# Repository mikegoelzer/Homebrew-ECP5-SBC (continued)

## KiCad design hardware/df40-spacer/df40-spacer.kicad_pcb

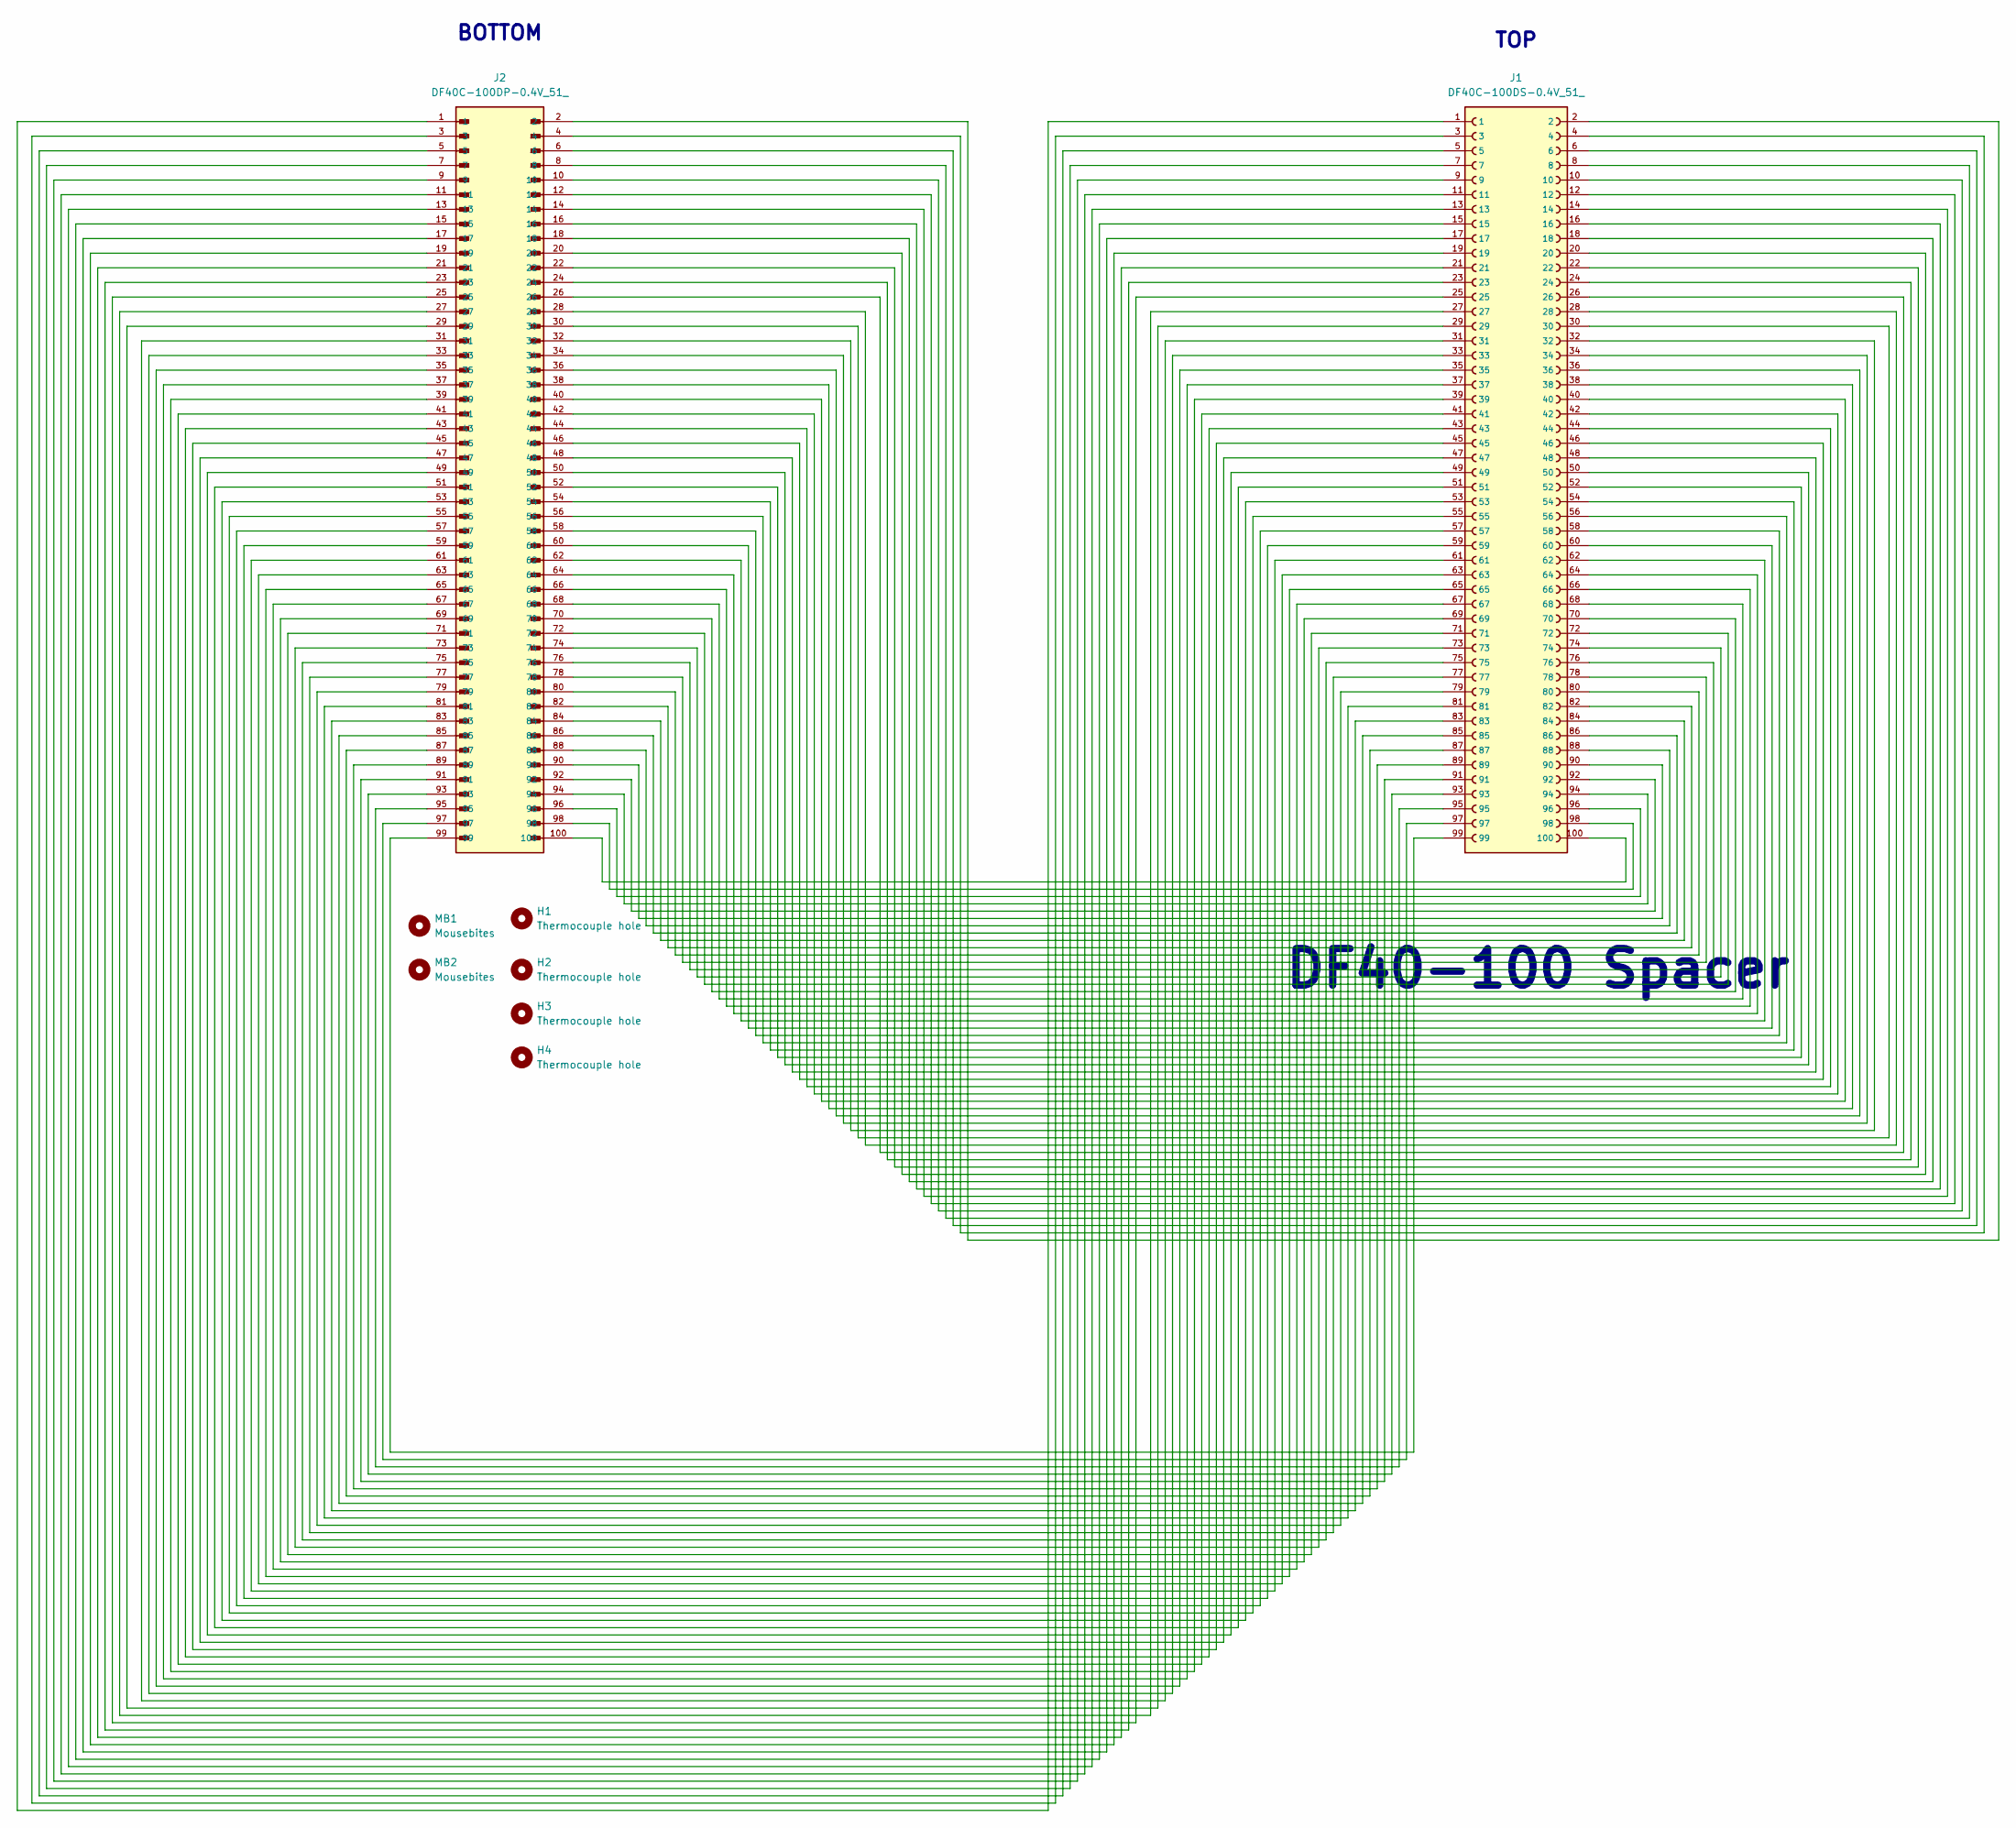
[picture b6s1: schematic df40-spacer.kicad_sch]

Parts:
H1, H2, H3, H4: Thermocouple hole; MountingHole_2.7mm_M2.5
J1: DF40C-100DS-0.4V_51_; HIROSE_DF40C-100DS-0.4V_51_; PARTREV Oct.1.2023
J2: DF40C-100DP-0.4V_51_; HIROSE_DF40C-100DP-0.4V_51_; MPN DF40C-100DP-0.4V(51)
MB1, MB2: Mousebites; mouse-bite-2.54mm-slot

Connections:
unnamed: J1.1, J2.1
unnamed: J1.2, J2.2
unnamed: J1.3, J2.3
unnamed: J1.4, J2.4
unnamed: J1.5, J2.5
unnamed: J1.6, J2.6
unnamed: J1.7, J2.7
unnamed: J1.8, J2.8
unnamed: J1.9, J2.9
unnamed: J1.10, J2.10
unnamed: J1.11, J2.11
unnamed: J1.12, J2.12
unnamed: J1.13, J2.13
unnamed: J1.14, J2.14
unnamed: J1.15, J2.15
unnamed: J1.16, J2.16
unnamed: J1.17, J2.17
unnamed: J1.18, J2.18
unnamed: J1.19, J2.19
unnamed: J1.20, J2.20
unnamed: J1.21, J2.21
unnamed: J1.22, J2.22
unnamed: J1.23, J2.23
unnamed: J1.24, J2.24
unnamed: J1.25, J2.25
unnamed: J1.26, J2.26
unnamed: J1.27, J2.27
unnamed: J1.28, J2.28
unnamed: J1.29, J2.29
unnamed: J1.30, J2.30
unnamed: J1.31, J2.31
unnamed: J1.32, J2.32
unnamed: J1.33, J2.33
unnamed: J1.34, J2.34
unnamed: J1.35, J2.35
unnamed: J1.36, J2.36
unnamed: J1.37, J2.37
unnamed: J1.38, J2.38
unnamed: J1.39, J2.39
unnamed: J1.40, J2.40
unnamed: J1.41, J2.41
unnamed: J1.42, J2.42
unnamed: J1.43, J2.43
unnamed: J1.44, J2.44
unnamed: J1.45, J2.45
unnamed: J1.46, J2.46
unnamed: J1.47, J2.47
unnamed: J1.48, J2.48
unnamed: J1.49, J2.49
unnamed: J1.50, J2.50
unnamed: J1.51, J2.51
unnamed: J1.52, J2.52
unnamed: J1.53, J2.53
unnamed: J1.54, J2.54
unnamed: J1.55, J2.55
unnamed: J1.56, J2.56
unnamed: J1.57, J2.57
unnamed: J1.58, J2.58
unnamed: J1.59, J2.59
unnamed: J1.60, J2.60
unnamed: J1.61, J2.61
unnamed: J1.62, J2.62
unnamed: J1.63, J2.63
unnamed: J1.64, J2.64
unnamed: J1.65, J2.65
unnamed: J1.66, J2.66
unnamed: J1.67, J2.67
unnamed: J1.68, J2.68
unnamed: J1.69, J2.69
unnamed: J1.70, J2.70
unnamed: J1.71, J2.71
unnamed: J1.72, J2.72
unnamed: J1.73, J2.73
unnamed: J1.74, J2.74
unnamed: J1.75, J2.75
unnamed: J1.76, J2.76
unnamed: J1.77, J2.77
unnamed: J1.78, J2.78
unnamed: J1.79, J2.79
unnamed: J1.80, J2.80
unnamed: J1.81, J2.81
unnamed: J1.82, J2.82
unnamed: J1.83, J2.83
unnamed: J1.84, J2.84
unnamed: J1.85, J2.85
unnamed: J1.86, J2.86
unnamed: J1.87, J2.87
unnamed: J1.88, J2.88
unnamed: J1.89, J2.89
unnamed: J1.90, J2.90
unnamed: J1.91, J2.91
unnamed: J1.92, J2.92
unnamed: J1.93, J2.93
unnamed: J1.94, J2.94
unnamed: J1.95, J2.95
unnamed: J1.96, J2.96
unnamed: J1.97, J2.97
unnamed: J1.98, J2.98
unnamed: J1.99, J2.99
unnamed: J1.100, J2.100

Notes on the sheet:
DF40-100 Spacer
TOP
BOTTOM

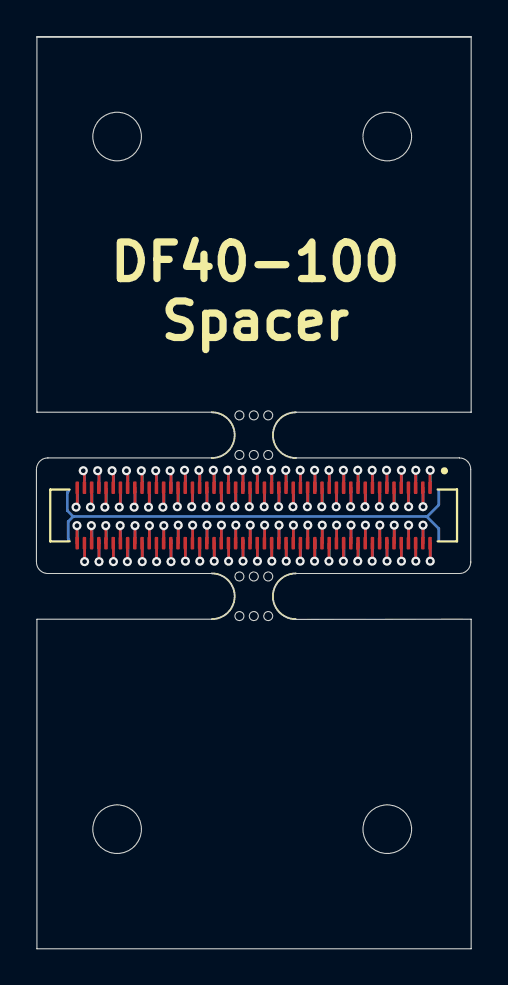
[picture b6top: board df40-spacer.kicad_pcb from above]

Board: 2 copper layers, 24.2 x 50.7 mm, 8 parts (1 on the bottom side), 100 nets.

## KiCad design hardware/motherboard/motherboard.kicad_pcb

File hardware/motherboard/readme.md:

# Motherboard

This is the motherboard of the computer.  The Compute Module snaps into it to provide the computer's CPU and memory.  The motherboard then provides:

- HDMI
- VGA
- JTAG
- USB debug interface
- PMOD connectors
- Expansion slots for custom PCBs
- FFC connector to connect to the hat board that provides the touch screen
- SD card slot for the computer's "hard drive"
- Boot flash for the FPGA
- 5V power input
- Diagnostic LEDs and switches
- 100-pin Hirose female connectors for the Compute Module to snap into

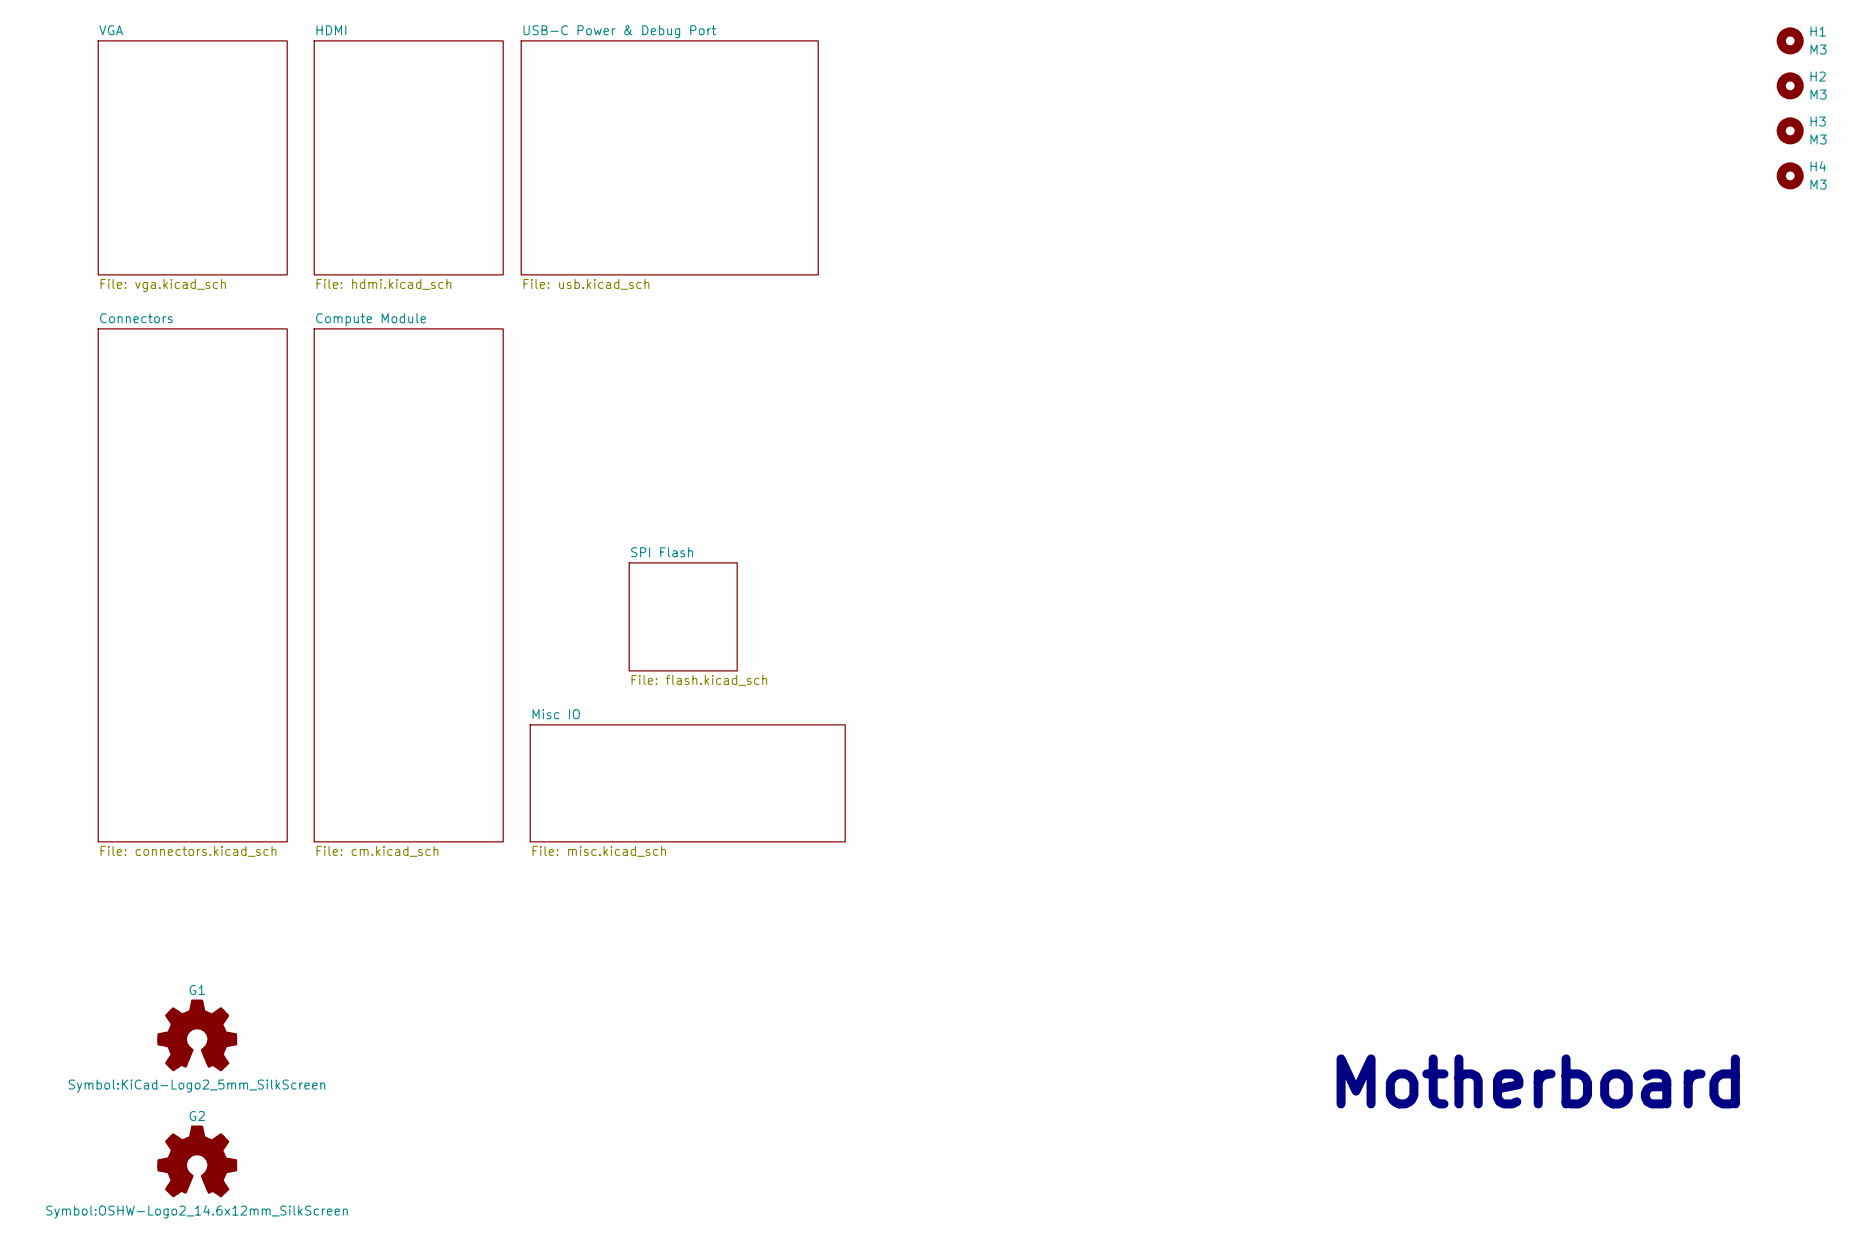
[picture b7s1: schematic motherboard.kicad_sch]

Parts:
G1: Logo_Open_Hardware_Small; KiCad-Logo2_5mm_SilkScreen
G2: Logo_Open_Hardware_Small; OSHW-Logo2_14.6x12mm_SilkScreen
H1, H2, H3, H4: M3; MountingHole_3.2mm_M3; MPN 97790603111

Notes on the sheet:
Motherboard

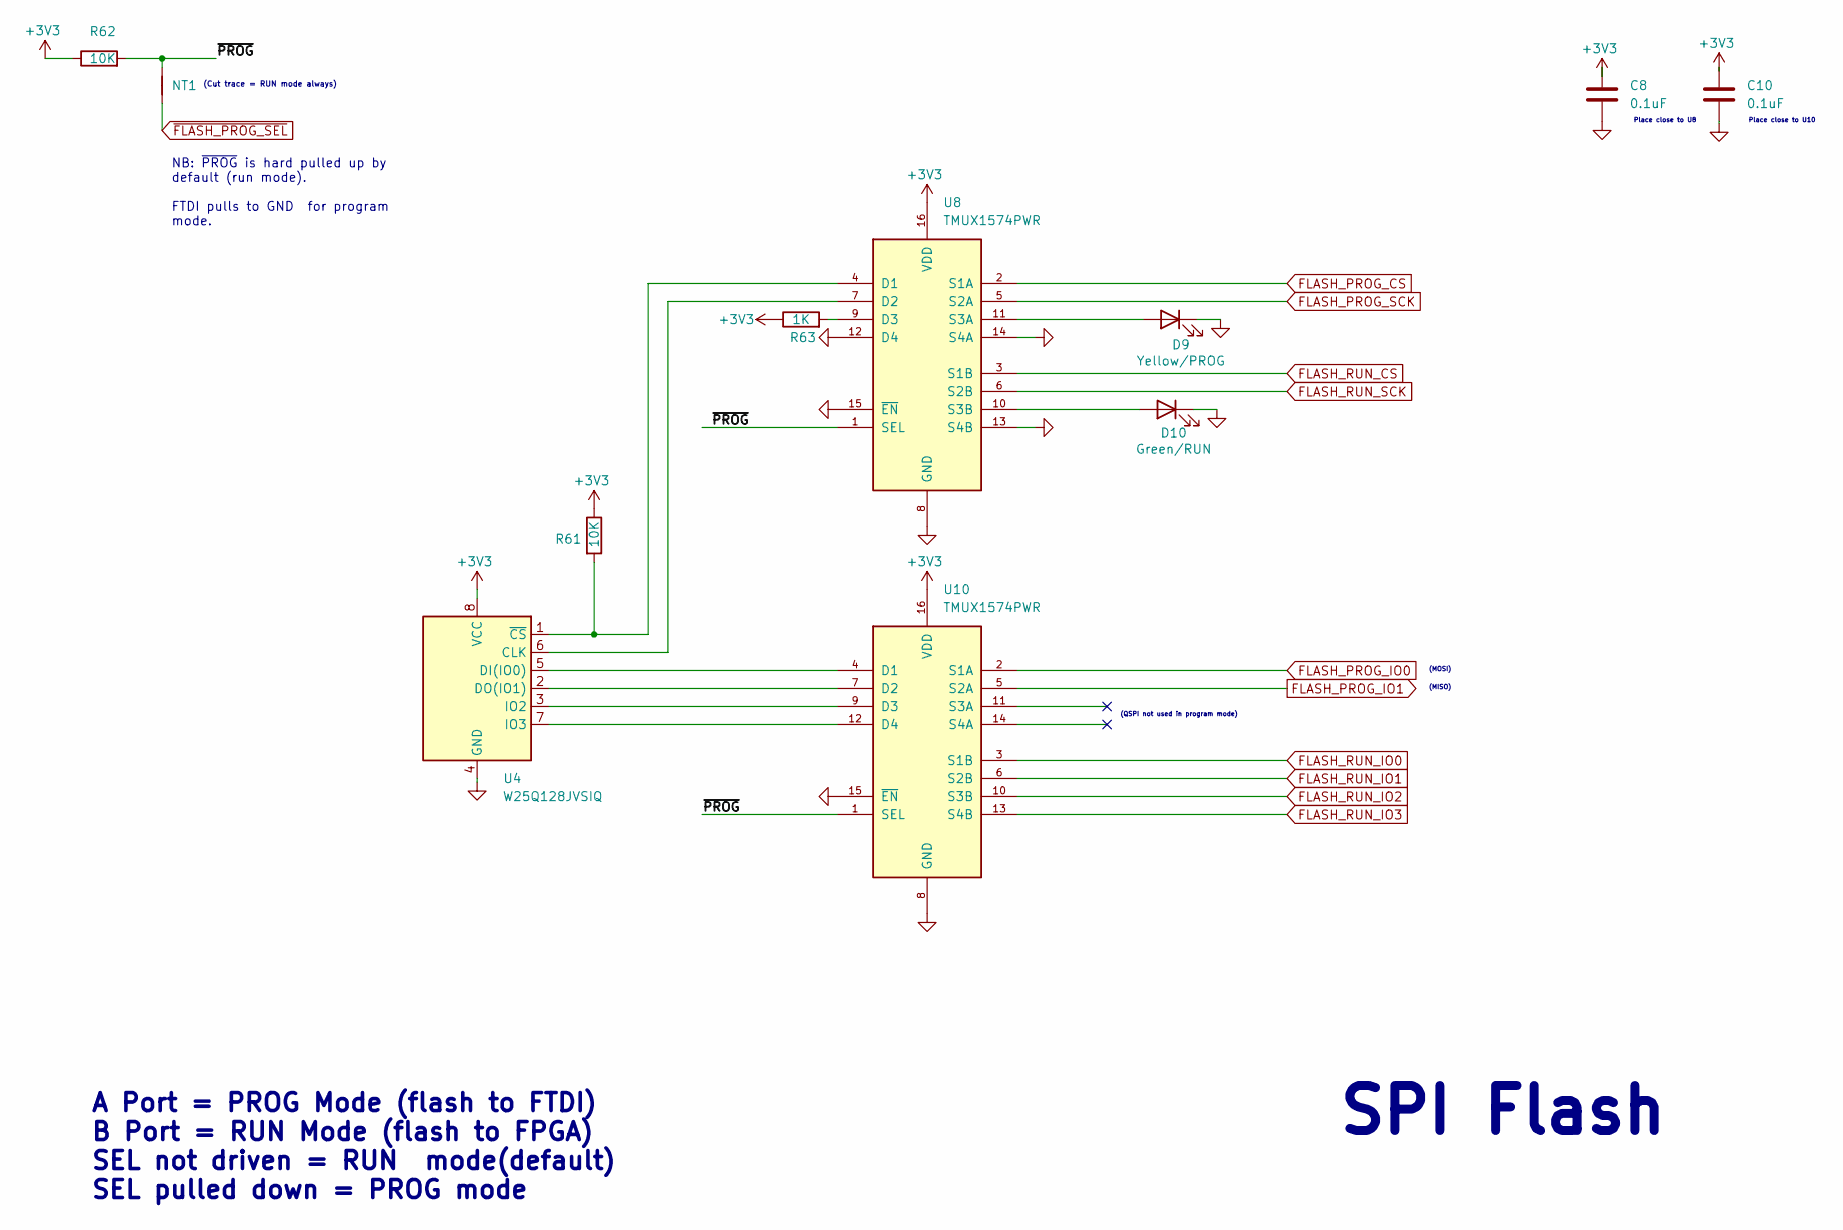
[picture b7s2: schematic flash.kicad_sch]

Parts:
C8, C10: 0.1uF; C_0805_2012Metric_Pad1.18x1.45mm_HandSolder; MPN CC0805KRX7R9BB104
D9: Yellow/PROG; LED_0805_2012Metric_Pad1.15x1.40mm_HandSolder; MPN 150080YS75000
D10: Green/RUN; LED_0805_2012Metric_Pad1.15x1.40mm_HandSolder; MPN 150080VS75000
NT1: NetTie_2; Solder_Jumper_Cuttable_6mil
R61, R62: 10K; R_0805_2012Metric_Pad1.15x1.40mm_HandSolder; MPN RC0805FR-0710KL
R63: 1K; R_0805_2012Metric_Pad1.15x1.40mm_HandSolder; MPN RC0805FR-071KL
U4: W25Q128JVSIQ; SOIC-8_5.23x5.23mm_P1.27mm; MPN W25Q128JVSIQ
U8, U10: TMUX1574PWR; SOP65P640X120-16N; MPN TMUX1574PWR

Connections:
+3V3: C8.1, C10.1, R61.1, R62.1, R63.1, U4.8 (VCC), U8.16 (VDD), U10.16 (VDD); also elsewhere on the board
/SPI Flash/~PROG: NT1.2, R62.2, U8.1 (SEL), U10.1 (SEL)
FLASH_PROG_CS: U8.2 (S1A); also elsewhere on the board
FLASH_PROG_IO0: U10.2 (S1A); also elsewhere on the board
FLASH_PROG_IO1: U10.5 (S2A); also elsewhere on the board
FLASH_PROG_SCK: U8.5 (S2A); also elsewhere on the board
FLASH_RUN_CS: U8.3 (S1B); also elsewhere on the board
FLASH_RUN_IO0: U10.3 (S1B); also elsewhere on the board
FLASH_RUN_IO1: U10.6 (S2B); also elsewhere on the board
FLASH_RUN_IO2: U10.10 (S3B); also elsewhere on the board
FLASH_RUN_IO3: U10.13 (S4B); also elsewhere on the board
FLASH_RUN_SCK: U8.6 (S2B); also elsewhere on the board
GND: C8.2, C10.2, D9.1 (K), D10.1 (K), U4.4 (GND), U8.8 (GND), U8.12 (D4), U8.13 (S4B), U8.14 (S4A), U8.15 (~EN), U10.8 (GND), U10.15 (~EN); also elsewhere on the board
unnamed: D9.2 (A), U8.11 (S3A)
unnamed: D10.2 (A), U8.10 (S3B)
unnamed: U4.6 (CLK), U8.7 (D2)
unnamed: R61.2, U4.1 (~CS), U8.4 (D1)
unnamed: R63.2, U8.9 (D3)
unnamed: U4.5 (DI(IO0)), U10.4 (D1)
unnamed: U4.2 (DO(IO1)), U10.7 (D2)
unnamed: U4.3 (IO2), U10.9 (D3)
unnamed: U4.7 (IO3), U10.12 (D4)
~FLASH_PROG_SEL: NT1.1; also elsewhere on the board

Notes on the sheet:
(QSPI not used in program mode)
A Port = PROG Mode (flash to FTDI) B Port = RUN Mode (flash to FPGA) SEL not driven = RUN mode(default) SEL pulled down = PROG mode
Place close to U8
(MOSI)
NB: ~{PROG} is hard pulled up by default (run mode). FTDI pulls to GND for program mode.
(MISO)
(Cut trace = RUN mode always)
SPI Flash
Place close to U10

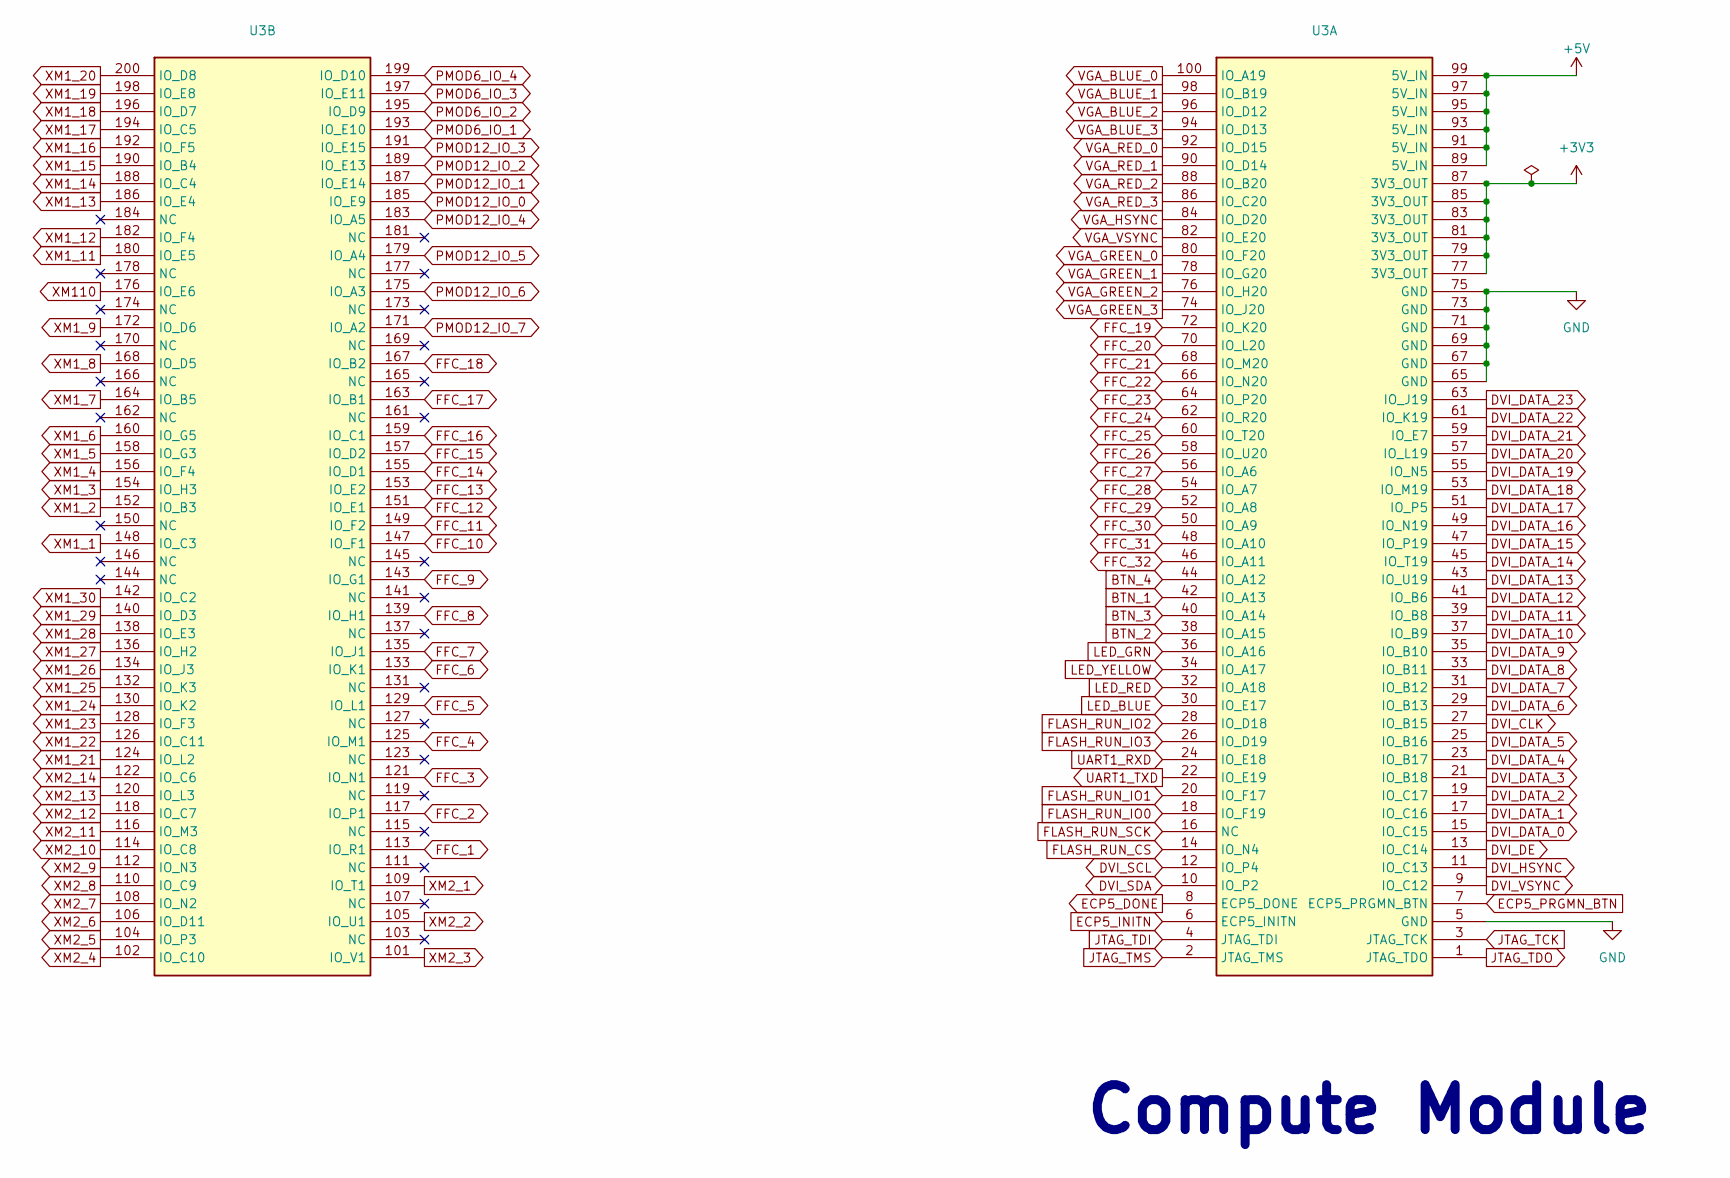
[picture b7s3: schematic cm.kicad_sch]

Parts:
U3: Goelzer_Compute_Module_Rev_1; MPN DF40C-100DS-0.4V(51)

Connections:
+3V3: U3.77 (3V3_OUT), U3.79 (3V3_OUT), U3.81 (3V3_OUT), U3.83 (3V3_OUT), U3.85 (3V3_OUT), U3.87 (3V3_OUT); also elsewhere on the board
+5V: U3.89 (5V_IN), U3.91 (5V_IN), U3.93 (5V_IN), U3.95 (5V_IN), U3.97 (5V_IN), U3.99 (5V_IN); also elsewhere on the board
BTN_1: U3.42 (IO_A13); also elsewhere on the board
BTN_2: U3.38 (IO_A15); also elsewhere on the board
BTN_3: U3.40 (IO_A14); also elsewhere on the board
BTN_4: U3.44 (IO_A12); also elsewhere on the board
DVI_CLK: U3.27 (IO_B15); also elsewhere on the board
DVI_DATA_0: U3.15 (IO_C15); also elsewhere on the board
DVI_DATA_1: U3.17 (IO_C16); also elsewhere on the board
DVI_DATA_2: U3.19 (IO_C17); also elsewhere on the board
DVI_DATA_3: U3.21 (IO_B18); also elsewhere on the board
DVI_DATA_4: U3.23 (IO_B17); also elsewhere on the board
DVI_DATA_5: U3.25 (IO_B16); also elsewhere on the board
DVI_DATA_6: U3.29 (IO_B13); also elsewhere on the board
DVI_DATA_7: U3.31 (IO_B12); also elsewhere on the board
DVI_DATA_8: U3.33 (IO_B11); also elsewhere on the board
DVI_DATA_9: U3.35 (IO_B10); also elsewhere on the board
DVI_DATA_10: U3.37 (IO_B9); also elsewhere on the board
DVI_DATA_11: U3.39 (IO_B8); also elsewhere on the board
DVI_DATA_12: U3.41 (IO_B6); also elsewhere on the board
DVI_DATA_13: U3.43 (IO_U19); also elsewhere on the board
DVI_DATA_14: U3.45 (IO_T19); also elsewhere on the board
DVI_DATA_15: U3.47 (IO_P19); also elsewhere on the board
DVI_DATA_16: U3.49 (IO_N19); also elsewhere on the board
DVI_DATA_17: U3.51 (IO_P5); also elsewhere on the board
DVI_DATA_18: U3.53 (IO_M19); also elsewhere on the board
DVI_DATA_19: U3.55 (IO_N5); also elsewhere on the board
DVI_DATA_20: U3.57 (IO_L19); also elsewhere on the board
DVI_DATA_21: U3.59 (IO_E7); also elsewhere on the board
DVI_DATA_22: U3.61 (IO_K19); also elsewhere on the board
DVI_DATA_23: U3.63 (IO_J19); also elsewhere on the board
DVI_DE: U3.13 (IO_C14); also elsewhere on the board
DVI_HSYNC: U3.11 (IO_C13); also elsewhere on the board
DVI_SCL: U3.12 (IO_P4); also elsewhere on the board
DVI_SDA: U3.10 (IO_P2); also elsewhere on the board
DVI_VSYNC: U3.9 (IO_C12); also elsewhere on the board
ECP5_DONE: U3.8 (ECP5_DONE); also elsewhere on the board
ECP5_INITN: U3.6 (ECP5_INITN); also elsewhere on the board
ECP5_PRGMN_BTN: U3.7 (ECP5_PRGMN_BTN); also elsewhere on the board
FFC_1: U3.113 (IO_R1); also elsewhere on the board
FFC_2: U3.117 (IO_P1); also elsewhere on the board
FFC_3: U3.121 (IO_N1); also elsewhere on the board
FFC_4: U3.125 (IO_M1); also elsewhere on the board
FFC_5: U3.129 (IO_L1); also elsewhere on the board
FFC_6: U3.133 (IO_K1); also elsewhere on the board
FFC_7: U3.135 (IO_J1); also elsewhere on the board
FFC_8: U3.139 (IO_H1); also elsewhere on the board
FFC_9: U3.143 (IO_G1); also elsewhere on the board
FFC_10: U3.147 (IO_F1); also elsewhere on the board
FFC_11: U3.149 (IO_F2); also elsewhere on the board
FFC_12: U3.151 (IO_E1); also elsewhere on the board
FFC_13: U3.153 (IO_E2); also elsewhere on the board
FFC_14: U3.155 (IO_D1); also elsewhere on the board
FFC_15: U3.157 (IO_D2); also elsewhere on the board
FFC_16: U3.159 (IO_C1); also elsewhere on the board
FFC_17: U3.163 (IO_B1); also elsewhere on the board
FFC_18: U3.167 (IO_B2); also elsewhere on the board
FFC_19: U3.72 (IO_K20); also elsewhere on the board
FFC_20: U3.70 (IO_L20); also elsewhere on the board
FFC_21: U3.68 (IO_M20); also elsewhere on the board
FFC_22: U3.66 (IO_N20); also elsewhere on the board
FFC_23: U3.64 (IO_P20); also elsewhere on the board
FFC_24: U3.62 (IO_R20); also elsewhere on the board
FFC_25: U3.60 (IO_T20); also elsewhere on the board
FFC_26: U3.58 (IO_U20); also elsewhere on the board
FFC_27: U3.56 (IO_A6); also elsewhere on the board
FFC_28: U3.54 (IO_A7); also elsewhere on the board
FFC_29: U3.52 (IO_A8); also elsewhere on the board
FFC_30: U3.50 (IO_A9); also elsewhere on the board
FFC_31: U3.48 (IO_A10); also elsewhere on the board
FFC_32: U3.46 (IO_A11); also elsewhere on the board
FLASH_RUN_CS: U3.14 (IO_N4); also elsewhere on the board
FLASH_RUN_IO0: U3.18 (IO_F19); also elsewhere on the board
FLASH_RUN_IO1: U3.20 (IO_F17); also elsewhere on the board
FLASH_RUN_IO2: U3.28 (IO_D18); also elsewhere on the board
FLASH_RUN_IO3: U3.26 (IO_D19); also elsewhere on the board
FLASH_RUN_SCK: U3.16 (NC); also elsewhere on the board
GND: U3.5 (GND), U3.65 (GND), U3.67 (GND), U3.69 (GND), U3.71 (GND), U3.73 (GND), U3.75 (GND); also elsewhere on the board
JTAG_TCK: U3.3 (JTAG_TCK); also elsewhere on the board
JTAG_TDI: U3.4 (JTAG_TDI); also elsewhere on the board
JTAG_TDO: U3.1 (JTAG_TDO); also elsewhere on the board
JTAG_TMS: U3.2 (JTAG_TMS); also elsewhere on the board
LED_BLUE: U3.30 (IO_E17); also elsewhere on the board
LED_GRN: U3.36 (IO_A16); also elsewhere on the board
LED_RED: U3.32 (IO_A18); also elsewhere on the board
LED_YELLOW: U3.34 (IO_A17); also elsewhere on the board
PMOD6_IO_1: U3.193 (IO_E10); also elsewhere on the board
PMOD6_IO_2: U3.195 (IO_D9); also elsewhere on the board
PMOD6_IO_3: U3.197 (IO_E11); also elsewhere on the board
PMOD6_IO_4: U3.199 (IO_D10); also elsewhere on the board
PMOD12_IO_0: U3.185 (IO_E9); also elsewhere on the board
PMOD12_IO_1: U3.187 (IO_E14); also elsewhere on the board
PMOD12_IO_2: U3.189 (IO_E13); also elsewhere on the board
PMOD12_IO_3: U3.191 (IO_E15); also elsewhere on the board
PMOD12_IO_4: U3.183 (IO_A5); also elsewhere on the board
PMOD12_IO_5: U3.179 (IO_A4); also elsewhere on the board
PMOD12_IO_6: U3.175 (IO_A3); also elsewhere on the board
PMOD12_IO_7: U3.171 (IO_A2); also elsewhere on the board
UART1_RXD: U3.24 (IO_E18); also elsewhere on the board
UART1_TXD: U3.22 (IO_E19); also elsewhere on the board
VGA_BLUE_0: U3.100 (IO_A19); also elsewhere on the board
VGA_BLUE_1: U3.98 (IO_B19); also elsewhere on the board
VGA_BLUE_2: U3.96 (IO_D12); also elsewhere on the board
VGA_BLUE_3: U3.94 (IO_D13); also elsewhere on the board
VGA_GREEN_0: U3.80 (IO_F20); also elsewhere on the board
VGA_GREEN_1: U3.78 (IO_G20); also elsewhere on the board
VGA_GREEN_2: U3.76 (IO_H20); also elsewhere on the board
VGA_GREEN_3: U3.74 (IO_J20); also elsewhere on the board
VGA_HSYNC: U3.84 (IO_D20); also elsewhere on the board
VGA_RED_0: U3.92 (IO_D15); also elsewhere on the board
VGA_RED_1: U3.90 (IO_D14); also elsewhere on the board
VGA_RED_2: U3.88 (IO_B20); also elsewhere on the board
VGA_RED_3: U3.86 (IO_C20); also elsewhere on the board
VGA_VSYNC: U3.82 (IO_E20); also elsewhere on the board
XM1_1: U3.148 (IO_C3); also elsewhere on the board
XM1_2: U3.152 (IO_B3); also elsewhere on the board
XM1_3: U3.154 (IO_H3); also elsewhere on the board
XM1_4: U3.156 (IO_F4); also elsewhere on the board
XM1_5: U3.158 (IO_G3); also elsewhere on the board
XM1_6: U3.160 (IO_G5); also elsewhere on the board
XM1_7: U3.164 (IO_B5); also elsewhere on the board
XM1_8: U3.168 (IO_D5); also elsewhere on the board
XM1_9: U3.172 (IO_D6); also elsewhere on the board
XM1_11: U3.180 (IO_E5); also elsewhere on the board
XM1_12: U3.182 (IO_F4); also elsewhere on the board
XM1_13: U3.186 (IO_E4); also elsewhere on the board
XM1_14: U3.188 (IO_C4); also elsewhere on the board
XM1_15: U3.190 (IO_B4); also elsewhere on the board
XM1_16: U3.192 (IO_F5); also elsewhere on the board
XM1_17: U3.194 (IO_C5); also elsewhere on the board
XM1_18: U3.196 (IO_D7); also elsewhere on the board
XM1_19: U3.198 (IO_E8); also elsewhere on the board
XM1_20: U3.200 (IO_D8); also elsewhere on the board
XM1_21: U3.124 (IO_L2); also elsewhere on the board
XM1_22: U3.126 (IO_C11); also elsewhere on the board
XM1_23: U3.128 (IO_F3); also elsewhere on the board
XM1_24: U3.130 (IO_K2); also elsewhere on the board
XM1_25: U3.132 (IO_K3); also elsewhere on the board
XM1_26: U3.134 (IO_J3); also elsewhere on the board
XM1_27: U3.136 (IO_H2); also elsewhere on the board
XM1_28: U3.138 (IO_E3); also elsewhere on the board
XM1_29: U3.140 (IO_D3); also elsewhere on the board
XM1_30: U3.142 (IO_C2); also elsewhere on the board
XM2_1: U3.109 (IO_T1); also elsewhere on the board
XM2_2: U3.105 (IO_U1); also elsewhere on the board
XM2_3: U3.101 (IO_V1); also elsewhere on the board
XM2_4: U3.102 (IO_C10); also elsewhere on the board
XM2_5: U3.104 (IO_P3); also elsewhere on the board
XM2_6: U3.106 (IO_D11); also elsewhere on the board
XM2_7: U3.108 (IO_N2); also elsewhere on the board
XM2_8: U3.110 (IO_C9); also elsewhere on the board
XM2_9: U3.112 (IO_N3); also elsewhere on the board
XM2_10: U3.114 (IO_C8); also elsewhere on the board
XM2_11: U3.116 (IO_M3); also elsewhere on the board
XM2_12: U3.118 (IO_C7); also elsewhere on the board
XM2_13: U3.120 (IO_L3); also elsewhere on the board
XM2_14: U3.122 (IO_C6); also elsewhere on the board
XM110: U3.176 (IO_E6); also elsewhere on the board

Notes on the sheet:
Compute Module
